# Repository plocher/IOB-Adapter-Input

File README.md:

# IOB-Adapter-Generic
## License: CERN Open Hardware Licence v1.2

IOB Personality: Low Pass filtered Inputs

A 5x2 plug-in Low pass input filter, passes signals lower than 1Khz.

RC Filter: Input maxF of 1KHZ = 10uS
Protection for Schottkey: 12v / 82ohm = 146mA, BAT54S maxI = 200mA

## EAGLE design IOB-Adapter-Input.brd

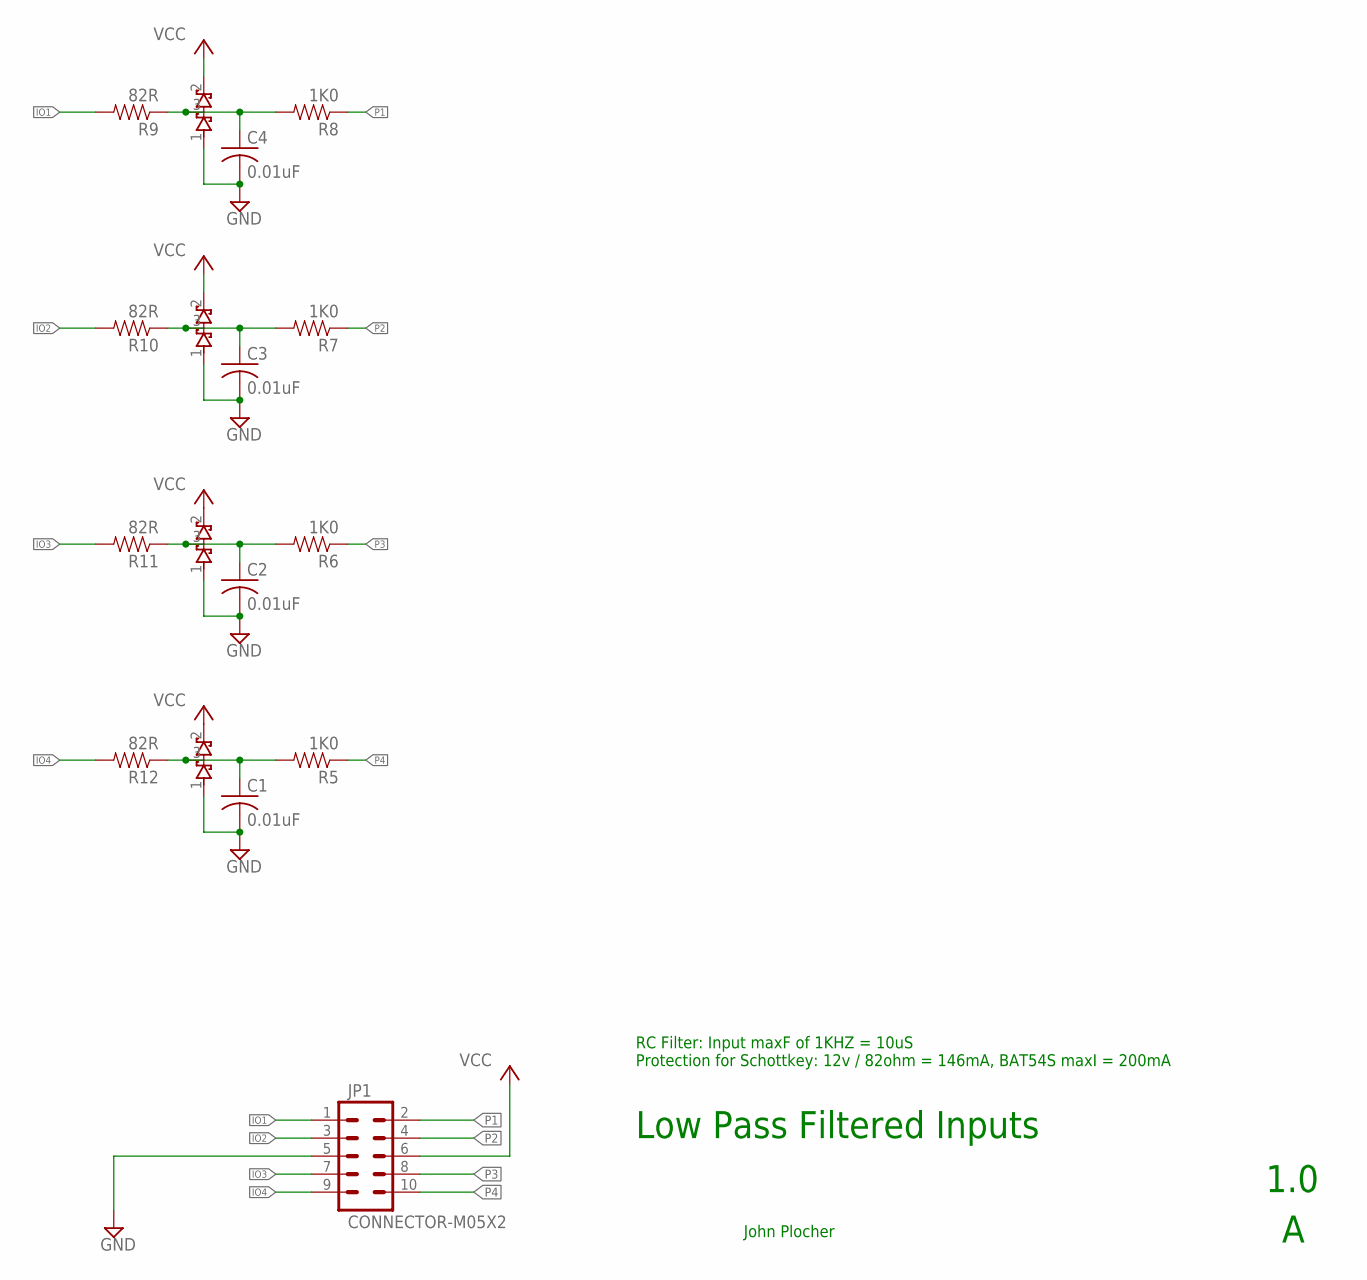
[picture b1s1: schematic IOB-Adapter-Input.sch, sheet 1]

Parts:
C1, C2, C3, C4: 0.01uF; 0603-CAP
D1, D2, D3, D4: BAT54S; SOT23
JP1: CONNECTOR-M05X2; IOB-V3-MODULE
R5, R6, R7, R8: 1K0; 0603-RES
R9, R10, R11, R12: 82R; 0805-RES

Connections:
GND: C1.2, C2.2, C3.2, C4.2, D1.1 (A1), D2.1 (A1), D3.1 (A1), D4.1 (A1), JP1.5
IO1: JP1.1, R9.2
IO2: JP1.3, R10.2
IO3: JP1.7, R11.2
IO4: JP1.9, R12.2
unnamed: C1.1, D1.3 (COM), R5.2, R12.1
unnamed: C2.1, D2.3 (COM), R6.2, R11.1
unnamed: C3.1, D3.3 (COM), R7.2, R10.1
unnamed: C4.1, D4.3 (COM), R8.2, R9.1
P1: JP1.2, R8.1
P2: JP1.4, R7.1
P3: JP1.8, R6.1
P4: JP1.10, R5.1
VCC: D1.2 (C2), D2.2 (C2), D3.2 (C2), D4.2 (C2), JP1.6

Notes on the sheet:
Low Pass Filtered Inputs
1.0
John Plocher
RC Filter: Input maxF of 1KHZ = 10uS Protection for Schottkey: 12v / 82ohm = 146mA, BAT54S maxI = 200mA

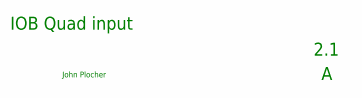
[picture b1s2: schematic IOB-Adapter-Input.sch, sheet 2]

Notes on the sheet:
IOB Quad input
2.1
John Plocher

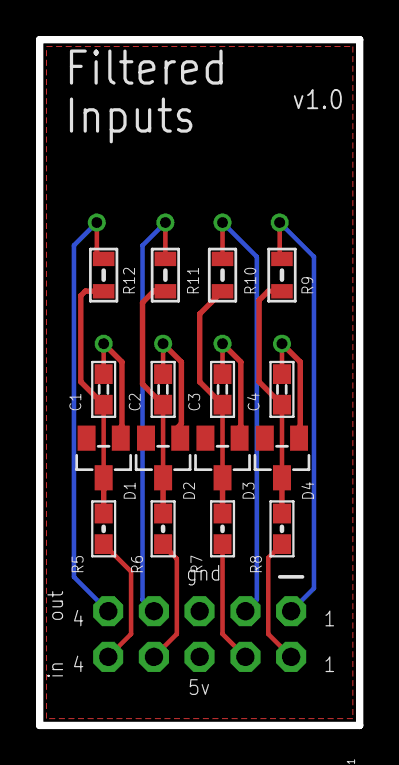
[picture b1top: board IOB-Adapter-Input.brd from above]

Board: 2 copper layers, 17.8 x 38.1 mm, 17 parts (1 on the bottom side), 14 nets.

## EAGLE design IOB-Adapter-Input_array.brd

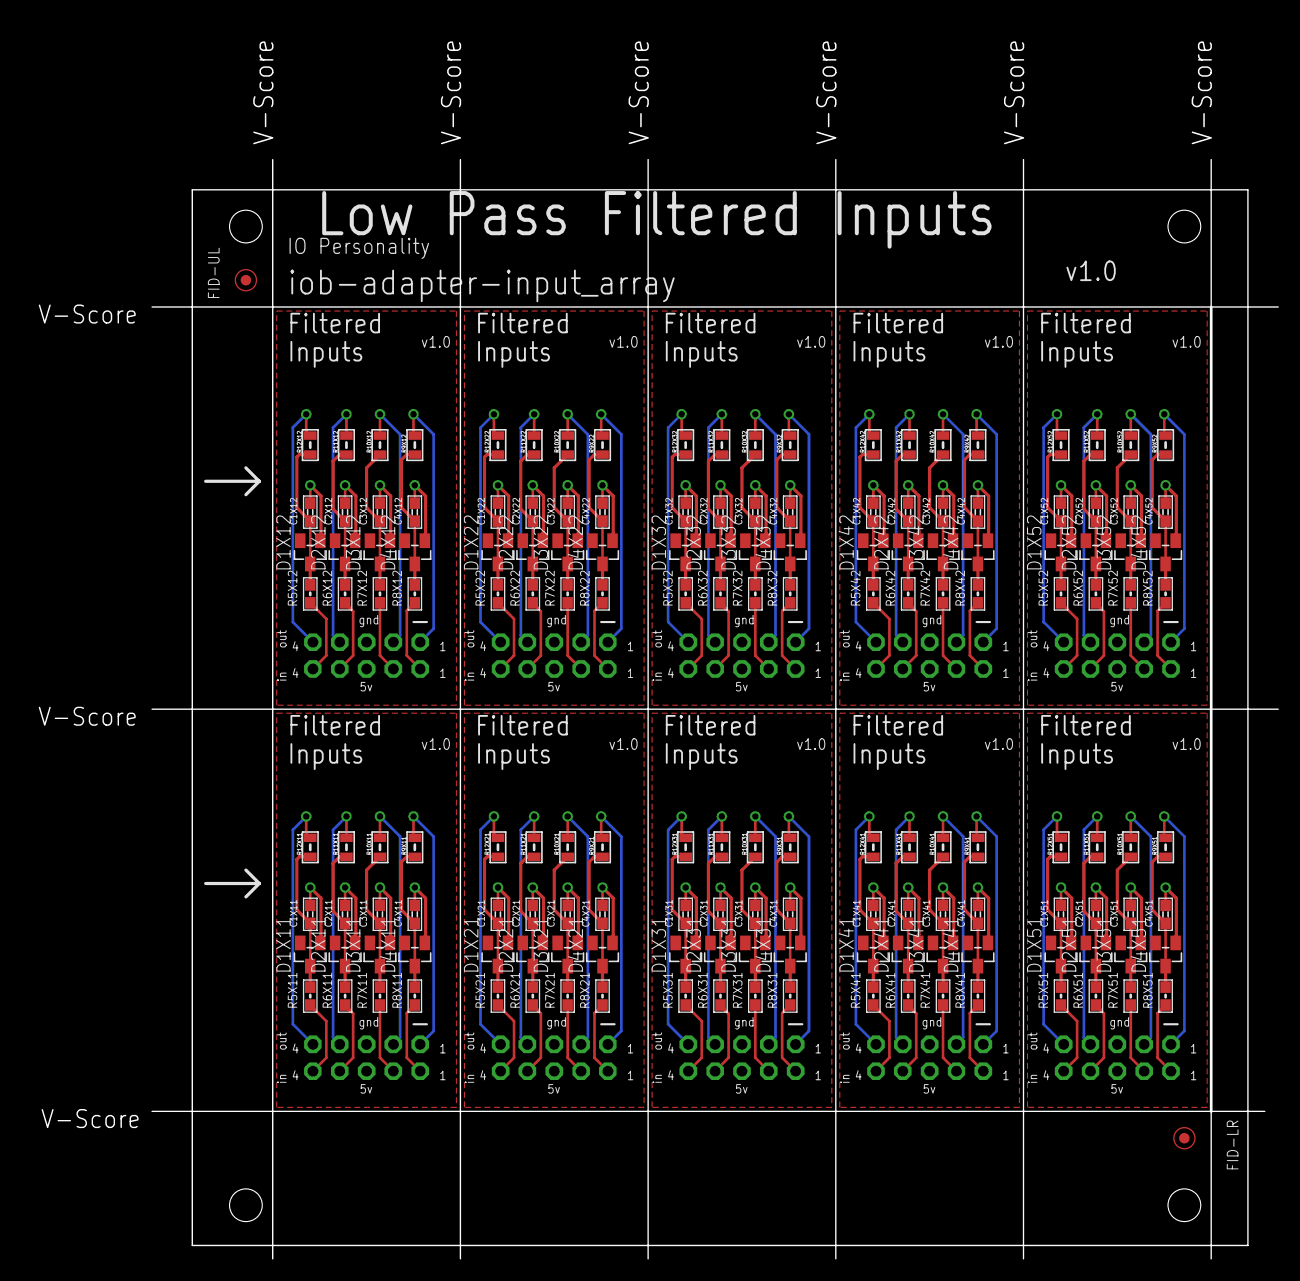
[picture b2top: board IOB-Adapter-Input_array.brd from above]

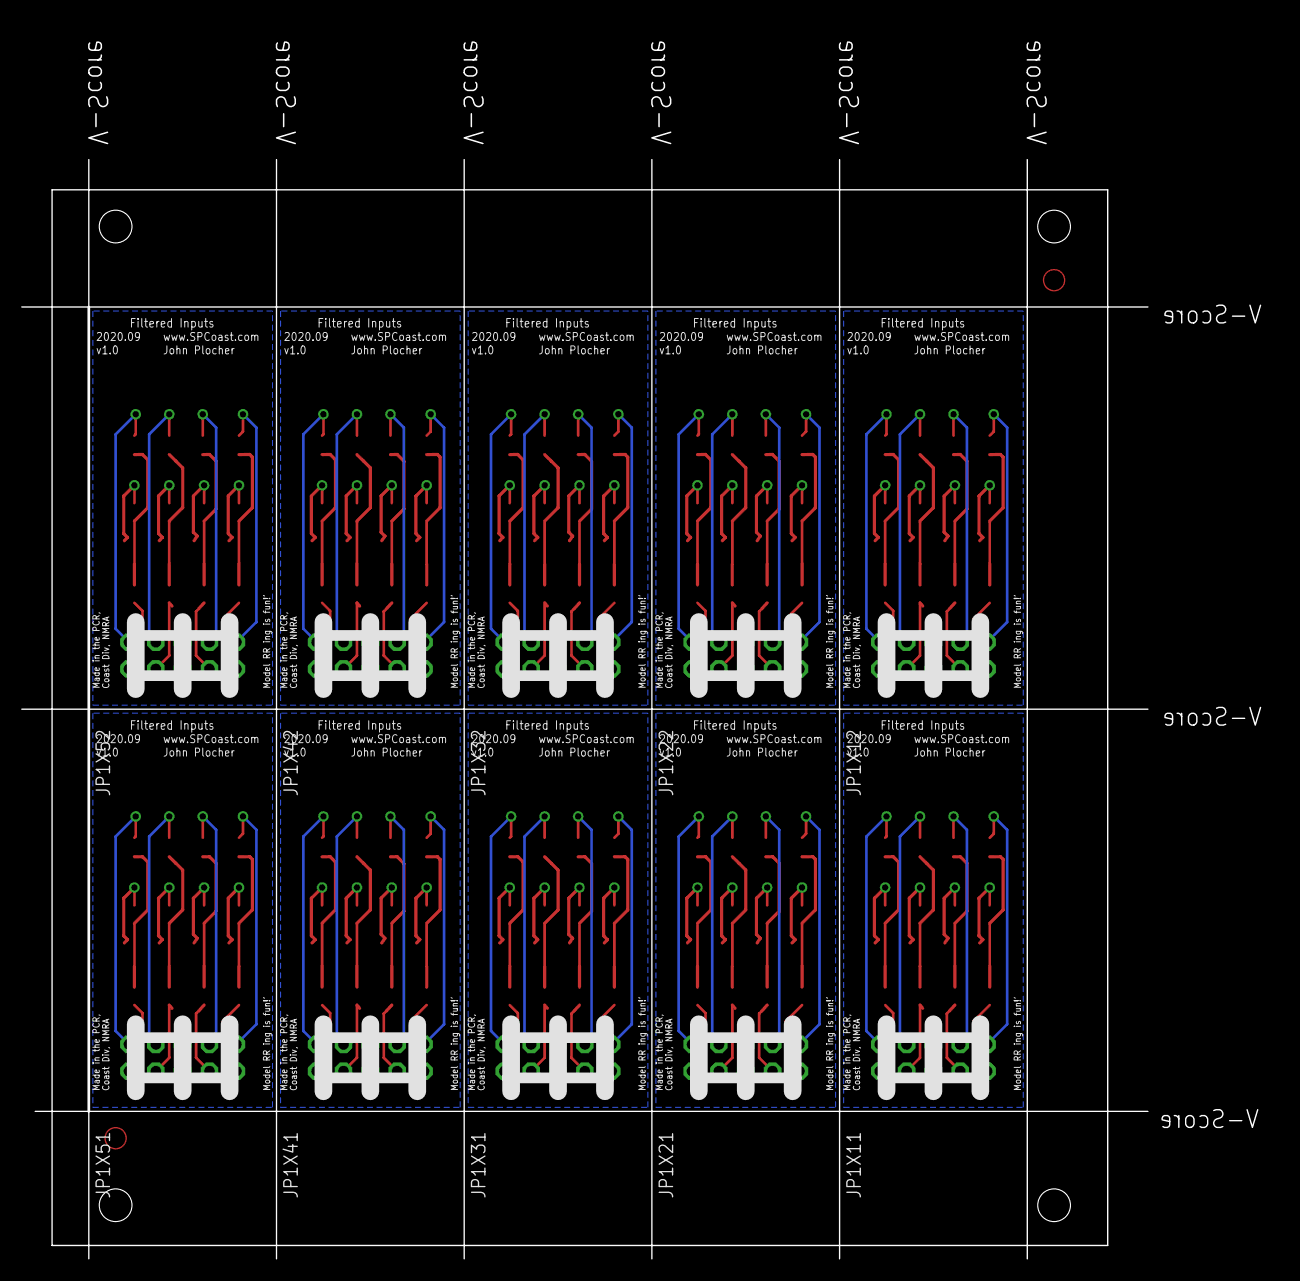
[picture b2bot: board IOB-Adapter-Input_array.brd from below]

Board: 2 copper layers, 118.9 x 117.1 mm, 173 parts (10 on the bottom side), 140 nets.

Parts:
C1X11, C1X12, C1X21, C1X22, C1X31, C1X32, C1X41, C1X42, C1X51, C1X52, C2X11, C2X12, C2X21, C2X22, C2X31, C2X32, C2X41, C2X42, C2X51, C2X52, C3X11, C3X12, C3X21, C3X22, C3X31, C3X32, C3X41, C3X42, C3X51, C3X52, C4X11, C4X12, C4X21, C4X22, C4X31, C4X32, C4X41, C4X42, C4X51, C4X52: 0.01uF; 0603-CAP
CARRIER: BOARD; BOARD-DINRAIL-3.17IN-5X2-IOP
D1X11, D1X12, D1X21, D1X22, D1X31, D1X32, D1X41, D1X42, D1X51, D1X52, D2X11, D2X12, D2X21, D2X22, D2X31, D2X32, D2X41, D2X42, D2X51, D2X52, D3X11, D3X12, D3X21, D3X22, D3X31, D3X32, D3X41, D3X42, D3X51, D3X52, D4X11, D4X12, D4X21, D4X22, D4X31, D4X32, D4X41, D4X42, D4X51, D4X52: BAT54S; SOT23
FID-LR: FIDUCIAL; FIDUCIAL_1MM
FID-UL: FIDUCIAL; FIDUCIAL_1MM
JP1X11, JP1X12, JP1X21, JP1X22, JP1X31, JP1X32, JP1X41, JP1X42, JP1X51, JP1X52: CONNECTOR-M05X2; IOB-V3-MODULE
R5X11, R5X12, R5X21, R5X22, R5X31, R5X32, R5X41, R5X42, R5X51, R5X52, R6X11, R6X12, R6X21, R6X22, R6X31, R6X32, R6X41, R6X42, R6X51, R6X52, R7X11, R7X12, R7X21, R7X22, R7X31, R7X32, R7X41, R7X42, R7X51, R7X52, R8X11, R8X12, R8X21, R8X22, R8X31, R8X32, R8X41, R8X42, R8X51, R8X52: 1K0; 0603-RES
R9X11, R9X12, R9X21, R9X22, R9X31, R9X32, R9X41, R9X42, R9X51, R9X52, R10X11, R10X12, R10X21, R10X22, R10X31, R10X32, R10X41, R10X42, R10X51, R10X52, R11X11, R11X12, R11X21, R11X22, R11X31, R11X32, R11X41, R11X42, R11X51, R11X52, R12X11, R12X12, R12X21, R12X22, R12X31, R12X32, R12X41, R12X42, R12X51, R12X52: 82R; 0805-RES

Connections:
GNDX11: C1X11.2, C2X11.2, C3X11.2, C4X11.2, D1X11.1, D2X11.1, D3X11.1, D4X11.1, JP1X11.5
GNDX12: C1X12.2, C2X12.2, C3X12.2, C4X12.2, D1X12.1, D2X12.1, D3X12.1, D4X12.1, JP1X12.5
GNDX21: C1X21.2, C2X21.2, C3X21.2, C4X21.2, D1X21.1, D2X21.1, D3X21.1, D4X21.1, JP1X21.5
GNDX22: C1X22.2, C2X22.2, C3X22.2, C4X22.2, D1X22.1, D2X22.1, D3X22.1, D4X22.1, JP1X22.5
GNDX31: C1X31.2, C2X31.2, C3X31.2, C4X31.2, D1X31.1, D2X31.1, D3X31.1, D4X31.1, JP1X31.5
GNDX32: C1X32.2, C2X32.2, C3X32.2, C4X32.2, D1X32.1, D2X32.1, D3X32.1, D4X32.1, JP1X32.5
GNDX41: C1X41.2, C2X41.2, C3X41.2, C4X41.2, D1X41.1, D2X41.1, D3X41.1, D4X41.1, JP1X41.5
GNDX42: C1X42.2, C2X42.2, C3X42.2, C4X42.2, D1X42.1, D2X42.1, D3X42.1, D4X42.1, JP1X42.5
GNDX51: C1X51.2, C2X51.2, C3X51.2, C4X51.2, D1X51.1, D2X51.1, D3X51.1, D4X51.1, JP1X51.5
GNDX52: C1X52.2, C2X52.2, C3X52.2, C4X52.2, D1X52.1, D2X52.1, D3X52.1, D4X52.1, JP1X52.5
IO1X11: JP1X11.1, R9X11.2
IO1X12: JP1X12.1, R9X12.2
IO1X21: JP1X21.1, R9X21.2
IO1X22: JP1X22.1, R9X22.2
IO1X31: JP1X31.1, R9X31.2
IO1X32: JP1X32.1, R9X32.2
IO1X41: JP1X41.1, R9X41.2
IO1X42: JP1X42.1, R9X42.2
IO1X51: JP1X51.1, R9X51.2
IO1X52: JP1X52.1, R9X52.2
IO2X11: JP1X11.3, R10X11.2
IO2X12: JP1X12.3, R10X12.2
IO2X21: JP1X21.3, R10X21.2
IO2X22: JP1X22.3, R10X22.2
IO2X31: JP1X31.3, R10X31.2
IO2X32: JP1X32.3, R10X32.2
IO2X41: JP1X41.3, R10X41.2
IO2X42: JP1X42.3, R10X42.2
IO2X51: JP1X51.3, R10X51.2
IO2X52: JP1X52.3, R10X52.2
IO3X11: JP1X11.7, R11X11.2
IO3X12: JP1X12.7, R11X12.2
IO3X21: JP1X21.7, R11X21.2
IO3X22: JP1X22.7, R11X22.2
IO3X31: JP1X31.7, R11X31.2
IO3X32: JP1X32.7, R11X32.2
IO3X41: JP1X41.7, R11X41.2
IO3X42: JP1X42.7, R11X42.2
IO3X51: JP1X51.7, R11X51.2
IO3X52: JP1X52.7, R11X52.2
IO4X11: JP1X11.9, R12X11.2
IO4X12: JP1X12.9, R12X12.2
IO4X21: JP1X21.9, R12X21.2
IO4X22: JP1X22.9, R12X22.2
IO4X31: JP1X31.9, R12X31.2
IO4X32: JP1X32.9, R12X32.2
IO4X41: JP1X41.9, R12X41.2
IO4X42: JP1X42.9, R12X42.2
IO4X51: JP1X51.9, R12X51.2
IO4X52: JP1X52.9, R12X52.2
unnamed: C1X11.1, D1X11.3, R5X11.2, R12X11.1
unnamed: C1X12.1, D1X12.3, R5X12.2, R12X12.1
unnamed: C1X21.1, D1X21.3, R5X21.2, R12X21.1
unnamed: C1X22.1, D1X22.3, R5X22.2, R12X22.1
unnamed: C1X31.1, D1X31.3, R5X31.2, R12X31.1
unnamed: C1X32.1, D1X32.3, R5X32.2, R12X32.1
unnamed: C1X41.1, D1X41.3, R5X41.2, R12X41.1
unnamed: C1X42.1, D1X42.3, R5X42.2, R12X42.1
unnamed: C1X51.1, D1X51.3, R5X51.2, R12X51.1
unnamed: C1X52.1, D1X52.3, R5X52.2, R12X52.1
unnamed: C2X11.1, D2X11.3, R6X11.2, R11X11.1
unnamed: C2X12.1, D2X12.3, R6X12.2, R11X12.1
unnamed: C2X21.1, D2X21.3, R6X21.2, R11X21.1
unnamed: C2X22.1, D2X22.3, R6X22.2, R11X22.1
unnamed: C2X31.1, D2X31.3, R6X31.2, R11X31.1
unnamed: C2X32.1, D2X32.3, R6X32.2, R11X32.1
unnamed: C2X41.1, D2X41.3, R6X41.2, R11X41.1
unnamed: C2X42.1, D2X42.3, R6X42.2, R11X42.1
unnamed: C2X51.1, D2X51.3, R6X51.2, R11X51.1
unnamed: C2X52.1, D2X52.3, R6X52.2, R11X52.1
unnamed: C3X11.1, D3X11.3, R7X11.2, R10X11.1
unnamed: C3X12.1, D3X12.3, R7X12.2, R10X12.1
unnamed: C3X21.1, D3X21.3, R7X21.2, R10X21.1
unnamed: C3X22.1, D3X22.3, R7X22.2, R10X22.1
unnamed: C3X31.1, D3X31.3, R7X31.2, R10X31.1
unnamed: C3X32.1, D3X32.3, R7X32.2, R10X32.1
unnamed: C3X41.1, D3X41.3, R7X41.2, R10X41.1
unnamed: C3X42.1, D3X42.3, R7X42.2, R10X42.1
unnamed: C3X51.1, D3X51.3, R7X51.2, R10X51.1
unnamed: C3X52.1, D3X52.3, R7X52.2, R10X52.1
unnamed: C4X11.1, D4X11.3, R8X11.2, R9X11.1
unnamed: C4X12.1, D4X12.3, R8X12.2, R9X12.1
unnamed: C4X21.1, D4X21.3, R8X21.2, R9X21.1
unnamed: C4X22.1, D4X22.3, R8X22.2, R9X22.1
unnamed: C4X31.1, D4X31.3, R8X31.2, R9X31.1
unnamed: C4X32.1, D4X32.3, R8X32.2, R9X32.1
unnamed: C4X41.1, D4X41.3, R8X41.2, R9X41.1
unnamed: C4X42.1, D4X42.3, R8X42.2, R9X42.1
unnamed: C4X51.1, D4X51.3, R8X51.2, R9X51.1
unnamed: C4X52.1, D4X52.3, R8X52.2, R9X52.1
P1X11: JP1X11.2, R8X11.1
P1X12: JP1X12.2, R8X12.1
P1X21: JP1X21.2, R8X21.1
P1X22: JP1X22.2, R8X22.1
P1X31: JP1X31.2, R8X31.1
P1X32: JP1X32.2, R8X32.1
P1X41: JP1X41.2, R8X41.1
P1X42: JP1X42.2, R8X42.1
P1X51: JP1X51.2, R8X51.1
P1X52: JP1X52.2, R8X52.1
P2X11: JP1X11.4, R7X11.1
P2X12: JP1X12.4, R7X12.1
P2X21: JP1X21.4, R7X21.1
P2X22: JP1X22.4, R7X22.1
P2X31: JP1X31.4, R7X31.1
P2X32: JP1X32.4, R7X32.1
P2X41: JP1X41.4, R7X41.1
P2X42: JP1X42.4, R7X42.1
P2X51: JP1X51.4, R7X51.1
P2X52: JP1X52.4, R7X52.1
P3X11: JP1X11.8, R6X11.1
P3X12: JP1X12.8, R6X12.1
P3X21: JP1X21.8, R6X21.1
P3X22: JP1X22.8, R6X22.1
P3X31: JP1X31.8, R6X31.1
P3X32: JP1X32.8, R6X32.1
P3X41: JP1X41.8, R6X41.1
P3X42: JP1X42.8, R6X42.1
P3X51: JP1X51.8, R6X51.1
P3X52: JP1X52.8, R6X52.1
P4X11: JP1X11.10, R5X11.1
P4X12: JP1X12.10, R5X12.1
P4X21: JP1X21.10, R5X21.1
P4X22: JP1X22.10, R5X22.1
P4X31: JP1X31.10, R5X31.1
P4X32: JP1X32.10, R5X32.1
P4X41: JP1X41.10, R5X41.1
P4X42: JP1X42.10, R5X42.1
P4X51: JP1X51.10, R5X51.1
P4X52: JP1X52.10, R5X52.1
VCCX11: D1X11.2, D2X11.2, D3X11.2, D4X11.2, JP1X11.6
VCCX12: D1X12.2, D2X12.2, D3X12.2, D4X12.2, JP1X12.6
VCCX21: D1X21.2, D2X21.2, D3X21.2, D4X21.2, JP1X21.6
VCCX22: D1X22.2, D2X22.2, D3X22.2, D4X22.2, JP1X22.6
VCCX31: D1X31.2, D2X31.2, D3X31.2, D4X31.2, JP1X31.6
VCCX32: D1X32.2, D2X32.2, D3X32.2, D4X32.2, JP1X32.6
VCCX41: D1X41.2, D2X41.2, D3X41.2, D4X41.2, JP1X41.6
VCCX42: D1X42.2, D2X42.2, D3X42.2, D4X42.2, JP1X42.6
VCCX51: D1X51.2, D2X51.2, D3X51.2, D4X51.2, JP1X51.6
VCCX52: D1X52.2, D2X52.2, D3X52.2, D4X52.2, JP1X52.6

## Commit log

2020-09-17 Initial version
2020-10-05 added values for connectors
2020-10-06 normalized values
